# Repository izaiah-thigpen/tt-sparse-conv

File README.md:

# Sparsity-Aware Convolution Core

An 8-bit 3×3 convolution multiply-accumulate core for Tiny Tapeout (SkyWater 130 nm),
controlled over SPI. It skips the switching work of any tap whose pixel or weight is
zero, and counts how many it skipped. It is the silicon half of a wafer-map defect
classifier: on the trained network, 77% of taps have a zero operand.

- [Datasheet: how it works and how to test](docs/info.md)
- [From a wafer to a defect class](docs/wafer_to_class.md): the dataset, how a wafer becomes the network's input, and what each layer does, with pictures

## Layout

| Path | Contents |
| --- | --- |
| `src/project.v` | Tiny Tapeout top level (`tt_um_izaiah_thigpen_sparse_conv`) |
| `src/conv_chip.sv` | SPI interface, command decoder, weight registers |
| `src/mac_core.sv` | Multiply-accumulate core, zero-skip gating, skip counter, output stage |
| `test/test.py` | cocotb tests through the pins only, checked against `test/refmodel.py` |
| `test/refmodel.py` | Bit-exact integer model of the design |
| `test/test_host.py` | Runs the demo-board test program against the design |
| `host/` | Test kit for the fabricated chip: data-to-SPI converter, demo-board test program, test vectors ([guide](host/README.md)) |

## Testing the fabricated chip

See [host/README.md](host/README.md): copy four files and a folder to the Tiny Tapeout demo board and run
one command. It reports PASS or FAIL for every check.

## Run the tests locally

```
cd test
make
```

Needs Icarus Verilog and `pip install -r test/requirements.txt`.

## GitHub Actions

Every push runs the RTL tests, builds the layout with LibreLane, runs Tiny Tapeout's
precheck, reruns the tests on the gate-level netlist, and publishes a layout viewer.
The viewer needs GitHub Pages enabled: Settings → Pages → Source: GitHub Actions.

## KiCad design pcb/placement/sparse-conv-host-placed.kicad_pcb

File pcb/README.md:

# Host board for the sparsity-aware convolution chip

A replacement for the Tiny Tapeout demo board, built to measure the chip's power. It keeps the demo
board v3's RP2350B pin map, so Tiny Tapeout's MicroPython firmware and the `host/` test kit run on it
unchanged, and adds a TI INA228 power monitor on the chip's 1.8 V core supply.

Status: **schematic rev A done; KiCad 9 ERC has 0 errors; starting placement done (`placement/`); routing not started.**

## What is here

| Path | Contents |
| --- | --- |
| `sparse-conv-host/` | The KiCad project: open `sparse-conv-host.kicad_pro` in KiCad 9 (it upgrades the KiCad 7 files) |
| `sparse-conv-host/libs/` | Tiny Tapeout symbols (RP2350B, breakout socket, PMOD host) and footprints (Apache 2.0); `SparseConvHost.pretty` holds the two footprints KiCad 9's libraries lack (RP2350 inductor, INA228 VSSOP-10) |
| `sparse-conv-host-schematic.pdf` | The schematic, 5 pages |
| `gen/design.py` | The design as data: every part, value, footprint, part number and pin-to-net assignment |
| `gen/schgen.py`, `gen/symlib.py`, `gen/sexpr.py` | Writes the KiCad schematic from `design.py` |
| `gen/check_netlist.py`, `gen/check_footprints.py` | Checks KiCad's own exported netlist against the design |
| `placement/` | Starting placement: `sparse-conv-host-placed.kicad_pcb` (all 110 parts placed, 4 layers, design rules set), `placement.csv` (every part's X, Y and rotation) and `placement-preview.png` |
| `gen/placement/` | The script that makes them, from the demo board's arrangement (see its README) |

The schematic is generated, so change `design.py` and rerun `python gen/design.py` rather than editing
connections by hand. Moving symbols around in KiCad for readability is fine; it does not change the nets.
The sheets are drawn net-label style: each pin has a short wire and a label, so the connections are
exactly the ones in `design.py`.

## Sheets

1. **Power:** USB-C, polyfuse, ESD, TLV1117LV33 3.3 V LDO, power LEDs (as on the demo board).
2. **MCU:** RP2350B, W25Q32 flash, 12 MHz crystal, internal core regulator, BOOT and RESET buttons, SWD
   header (copied from the demo board's RP2350B sheet).
3. **Breakout:** the Hirose DF12 60+50-pin socket for the chip's breakout (`TT_HRS_CARRIER_REVC`), MUX
   pull-ups, project reset and clock, three PMOD sockets, a 2×8 logic-analyzer header, 10 MΩ pull-downs
   on the analog pins, mounting holes.
4. **Power monitor:** INA228 across a 0.499 Ω + 4.99 Ω shunt in the core supply, I2C on GPIO12/13,
   ALERT on GPIO15.

## Measuring the chip's core power

The breakout regulates the chip's 1.8 V core itself: AP2112K-1.8 → `VCC_REG` → R14 (0 Ω, 0805) →
`VCCD`. To route the core supply through this board's shunt:

1. On the breakout, remove R14 and solder a 1×12 header into J2.
2. Wire J2 pin 5 (`VCC_REG`) to CORE pin 1, J2 pin 6 (`VCCD`) to CORE pin 2, and ground to CORE pin 3.
3. Normal range: 5.49 Ω, 7.5 mA full scale, 14 nA per step. For more current, fit a jumper on RANGE
   (0.499 Ω, 82 mA full scale).

Without the wires and with R14 in place, the board works exactly like a demo board.

## Checks

- KiCad 7's netlist export reads all sheets; every one of the 99 design nets is one KiCad net with
  exactly the intended pins, every no-connect pin is alone, and no net has a single pin.
- ERC-style rules: every power-input pin has a driver or power flag; no two outputs share a net.
- All 63 used pins of the breakout socket match the Tiny Tapeout demo board, and the socket's power,
  ground, I/O and MUX pins were cross-checked against the SkyWater breakout rev 3.1 schematic.
- Every symbol pin has a pad of the same number in its footprint.

- KiCad 9 ERC: 0 errors. Remaining warnings are harmless: library-copy mismatches (the schematic embeds
  KiCad 7 copies of standard symbols), QSPI_IOVDD typed bidirectional in the Tiny Tapeout RP2350 symbol,
  and the breakout socket's hidden `3v3` pins merging into `+3V3`.

Run `kicad-cli sch export netlist -o board.net sparse-conv-host/sparse-conv-host.kicad_sch`, then
`python gen/check_netlist.py board.net` and `python gen/check_footprints.py`. Run KiCad 9's ERC as well
after opening the project.

## Open items

- Confirm this shuttle's chips ship on SkyWater breakout rev 3.1.
- JLCPCB sourcing for the Hirose DF12NB(5.0)-60DP and -50DP connectors, the RP2350B, the shunts and
  the 10 MΩ resistors (LCSC numbers are filled in only where verified).
- Board outline 100 × 85 mm, corner at (100, 100). The RP2350B sits under the breakout board, as on the demo board.
- Layout: 4 layers; Kelvin traces from the shunt pads to the INA228; follow Raspberry Pi's RP2350
  layout guidance for the crystal, flash and core regulator.

## KiCad 10 note

KiCad 10's `USB_C_Receptacle_HRO_TYPE-C-31-M-12` footprint names the shell pads `SH`; KiCad 7's
symbol calls the shield pin `S1`. In the project, J1's shield pin number was changed to `SH` in the
Symbol Editor so the shell connects to `USB_SHIELD`. If the schematic is ever regenerated from
`design.py`, make the same change again before updating the PCB.

Derived from the [Tiny Tapeout demo board](https://github.com/TinyTapeout/tt-demo-pcb) and
[breakout](https://github.com/TinyTapeout/breakout-pcb) designs, © 2024–2025 Pat Deegan / Psychogenic
Technologies, Apache 2.0.

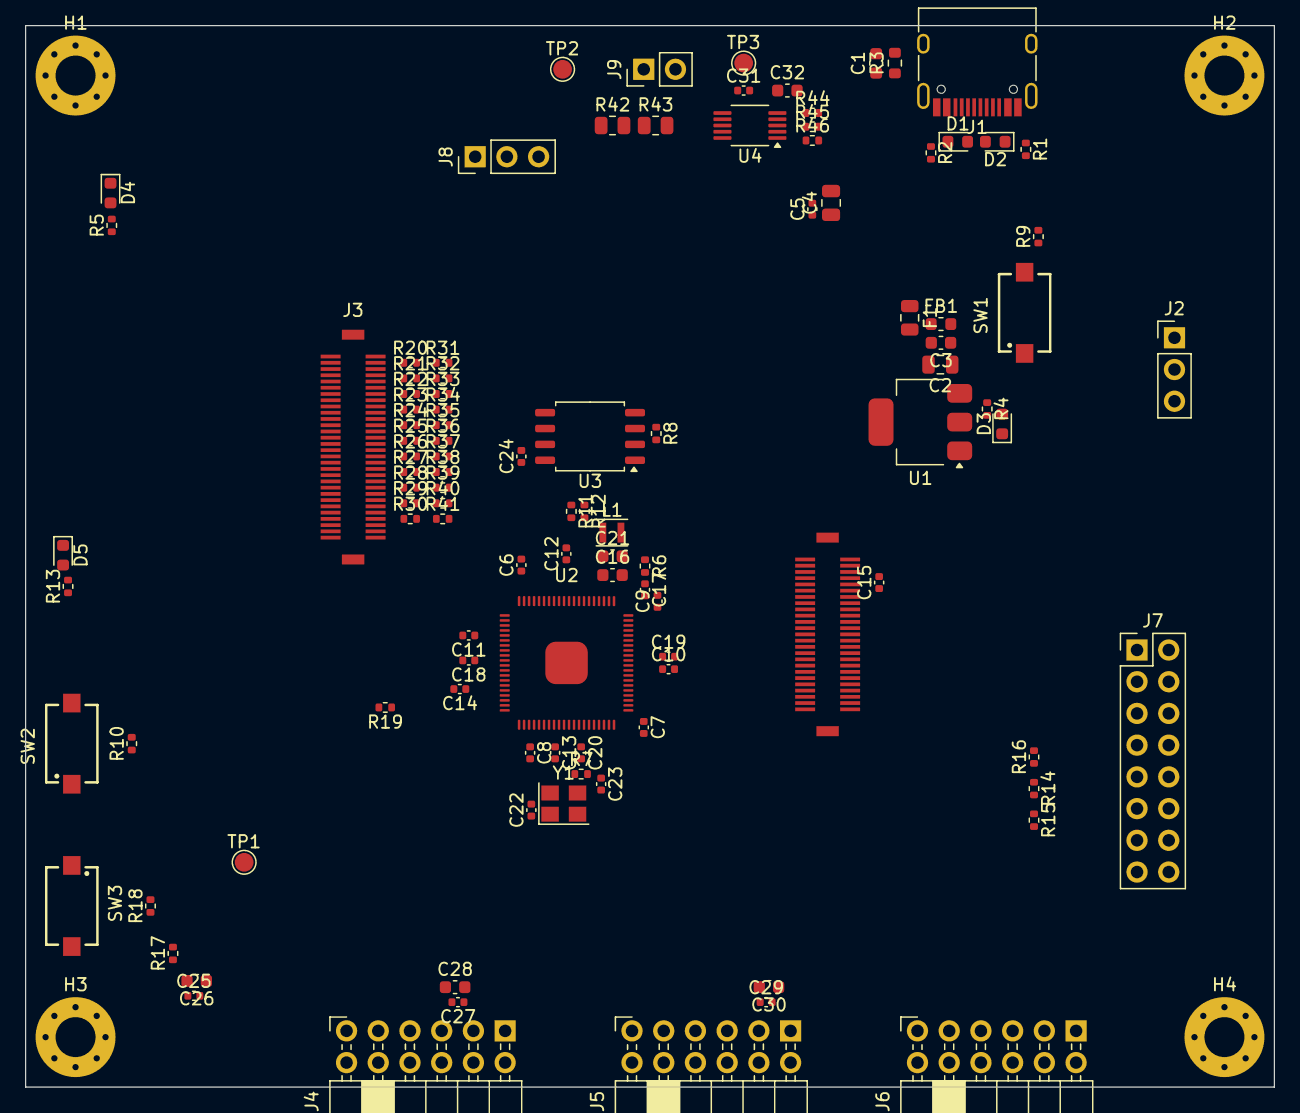
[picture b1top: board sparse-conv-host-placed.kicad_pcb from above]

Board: 4 copper layers, 100.0 x 85.0 mm, 110 parts (0 on the bottom side), 99 nets, no tracks yet.

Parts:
C1, C3, C16, C21, C26, C28, C30, C32: C_0603_1608Metric
C2, C4: C_0805_2012Metric
C5, C6, C7, C8, C9, C10, C11, C12, C13, C14, C15, C17, C18, C19, C20, C22, C23, C24, C25, C27, C29, C31: C_0402_1005Metric
D1, D2: D_0603_1608Metric
D3, D4, D5: LED_0603_1608Metric
F1: Fuse_0805_2012Metric
FB1: L_0603_1608Metric
H1, H2, H3, H4: MountingHole_3.2mm_M3_Pad_Via
J1: USB_C_Receptacle_HRO_TYPE-C-31-M-12
J2, J8: PinHeader_1x03_P2.54mm_Vertical
J3: TT; TT_HRS_CARRIER_REVC
J4, J5, J6: PinSocket_2x06_P2.54mm_PMODHost1A
J7: PinHeader_2x08_P2.54mm_Vertical
J9: PinHeader_1x02_P2.54mm_Vertical
L1: L_Murata_DFE201610P
R1, R2, R4, R5, R6, R7, R8, R9, R10, R11, R12, R13, R14, R15, R16, R17, R18, R19, R20, R21, R22, R23, R24, R25, R26, R27, R28, R29, R30, R31, R32, R33, R34, R35, R36, R37, R38, R39, R40, R41, R44, R45, R46: R_0402_1005Metric
R3: R_0603_1608Metric
R42, R43: R_0805_2012Metric
SW1, SW2, SW3: 434121025816
TP1, TP2, TP3: TestPoint_Pad_D1.5mm
U1: SOT-223-3_TabPin2
U2: QFN; QFN-80-1EP_10x10mm_P0.4mm_EP3.4x3.4mm
U3: SOIC-8_5.275x5.275mm_P1.27mm
U4: VSSOP-10_3x3mm_P0.5mm
Y1: Crystal_SMD_3225-4Pin_3.2x2.5mm

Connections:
+1V1: C18.1, C19.1, C20.1, C21.1, L1.1, U2.10, U2.32, U2.51, U2.65
+3V3: C4.1, C5.1, C6.1, C7.1, C8.1, C9.1, C10.1, C11.1, C12.1, C13.1, C14.1, C15.1, C16.1, C24.1, C25.1, C26.1, C27.1, C28.1, C29.1, C30.1, C31.1, C32.1, J3.L1, J3.R8, J3.R10, J4.6, J4.12, J5.6, J5.12, J6.6, J6.12, R5.1, R6.1, R8.1, R10.1, R14.1, R15.1, R16.1, R18.1, R44.1, R45.1, R46.1, U1.2, U2.5, U2.15, U2.24, U2.29, U2.41, U2.50, U2.59, U2.60, U2.64, U2.68, U2.69, U2.76, U3.8, U4.6
+5V: C2.1, C3.1, FB1.2, J3.R2, J3.R4, R4.1, U1.3
/Chip breakout sockets and I/O/AN0: J3.L2, R20.1
/Chip breakout sockets and I/O/AN1: J3.L4, R21.1
/Chip breakout sockets and I/O/AN2: J3.L6, R22.1
/Chip breakout sockets and I/O/AN3: J3.L10, R23.1
/Chip breakout sockets and I/O/AN4: J3.L12, R24.1
/Chip breakout sockets and I/O/AN5: J3.L14, R25.1
/Chip breakout sockets and I/O/AN6: J3.L18, R26.1
/Chip breakout sockets and I/O/AN7: J3.L20, R27.1
/Chip breakout sockets and I/O/AN8: J3.L22, R28.1
/Chip breakout sockets and I/O/AN9: J3.L26, R29.1
/Chip breakout sockets and I/O/AN10: J3.L28, R30.1
/Chip breakout sockets and I/O/AN11: J3.L30, R31.1
/Chip breakout sockets and I/O/AN12: J3.L34, R32.1
/Chip breakout sockets and I/O/AN13: J3.L36, R33.1
/Chip breakout sockets and I/O/AN14: J3.L38, R34.1
/Chip breakout sockets and I/O/AN15: J3.L42, R35.1
/Chip breakout sockets and I/O/AN16: J3.L44, R36.1
/Chip breakout sockets and I/O/AN17: J3.L46, R37.1
/Chip breakout sockets and I/O/AN18: J3.L50, R38.1
/Chip breakout sockets and I/O/AN19: J3.L52, R39.1
/Chip breakout sockets and I/O/AN20: J3.L54, R40.1
/Chip breakout sockets and I/O/AN21: J3.L58, R41.1
/Chip breakout sockets and I/O/PROJ_CLK: J3.L57, J7.9, R19.2, TP1.1
/Chip breakout sockets and I/O/PROJ_RST_N: J3.L53, J7.11, R17.2, R18.2, SW3.1
/Chip core power monitor/SHUNT_MID: J9.1, R42.2, R43.1
/Chip core power monitor/VCORE_IN: J8.1, R42.1, TP2.1, U4.10
/Chip core power monitor/VCORE_OUT: J8.2, J9.2, R43.2, TP3.1, U4.8, U4.9
/RP2350B microcontroller/BOOT_SW: R9.2, SW1.1
/RP2350B microcontroller/QSPI_SCLK: U2.71, U3.6
/RP2350B microcontroller/QSPI_SD0: U2.72, U3.5
/RP2350B microcontroller/QSPI_SD1: U2.74, U3.2
/RP2350B microcontroller/QSPI_SD2: U2.73, U3.3
/RP2350B microcontroller/QSPI_SD3: U2.70, U3.7
/RP2350B microcontroller/QSPI_SS: R8.2, R9.1, U2.75, U3.1
/RP2350B microcontroller/RP_LED: R13.1, U2.9
/RP2350B microcontroller/RP_LED_A: D5.2, R13.2
/RP2350B microcontroller/RUN: R10.2, SW2.1, U2.35
/RP2350B microcontroller/SWCLK: J2.1, U2.33
/RP2350B microcontroller/SWDIO: J2.3, U2.34
/RP2350B microcontroller/USB_DM_MCU: R12.2, U2.66
/RP2350B microcontroller/USB_DP_MCU: R11.2, U2.67
/RP2350B microcontroller/VREG_AVDD: C17.1, R6.2, U2.61
/RP2350B microcontroller/VREG_LX: L1.2, U2.63
/RP2350B microcontroller/XIN: C22.1, U2.30, Y1.1
/RP2350B microcontroller/XOUT: R7.1, U2.31
/RP2350B microcontroller/XOUT_R: C23.1, R7.2, Y1.3
/USB-C input and 3.3 V supply/CC1: J1.A5, R1.1
/USB-C input and 3.3 V supply/CC2: J1.B5, R2.1
/USB-C input and 3.3 V supply/LED_3V3: D4.2, R5.2
/USB-C input and 3.3 V supply/LED_USB: D3.2, R4.2
/USB-C input and 3.3 V supply/USB_SHIELD: C1.1, J1.S1, R3.1
/USB-C input and 3.3 V supply/VBUS_F: F1.2, FB1.1
/USB-C input and 3.3 V supply/VBUS_RAW: F1.1, J1.A4, J1.A9, J1.B4, J1.B9
CTRL_ENA: J3.R46, R14.2, U2.77
CTRL_SEL_INC: J3.R47, R15.2, U2.79
CTRL_SEL_RST_N: J3.R43, R16.2, U2.78
GND: C1.2, C2.2, C3.2, C4.2, C5.2, C6.2, C7.2, C8.2, C9.2, C10.2, C11.2, C12.2, C13.2, C14.2, C15.2, C16.2, C17.2, C18.2, C19.2, C20.2, C21.2, C22.2, C23.2, C24.2, C25.2, C26.2, C27.2, C28.2, C29.2, C30.2, C31.2, C32.2, D1.2, D2.2, D3.1, D4.1, D5.1, H1.1, H2.1, H3.1, H4.1, J1.A1, J1.A12, J1.B1, J1.B12, J2.2, J3.L3, J3.L8, J3.L11, J3.L16, J3.L19, J3.L24, J3.L27, J3.L32, J3.L35, J3.L40, J3.L43, J3.L48, J3.L51, J3.L55, J3.L56, J3.L59, J3.R1, J3.R6, J3.R11, J3.R12, J3.R20, J3.R21, J3.R28, J3.R33, J3.R38, J3.R41, J3.R44, J3.R45, J3.R48, J4.5, J4.11, J5.5, J5.11, J6.5, J6.11, J7.13, J7.15, J8.3, R1.2, R2.2, R3.2, R20.2, R21.2, R22.2, R23.2, R24.2, R25.2, R26.2, R27.2, R28.2, R29.2, R30.2, R31.2, R32.2, R33.2, R34.2, R35.2, R36.2, R37.2, R38.2, R39.2, R40.2, R41.2, SW1.2, SW2.2, SW3.2, U1.1, U2.62, U2.81, U3.4, U4.1, U4.2, U4.7, Y1.2, Y1.4
I2C_SCL: R45.2, U2.12, U4.5
I2C_SDA: R44.2, U2.11, U4.4
MNG0: J3.R42, U2.80
MNG1: J3.R40, U2.1
MNG2: J3.R36, U2.2
MNG3: J3.R30, U2.3
MNG4: J3.R26, U2.4
MNG5: J3.R22, U2.6
MNG6: J3.R18, U2.7
MNG7: J3.R16, U2.8
PM_ALERT: R46.2, U2.14, U4.3
PROJ_CLK_RP: R19.1, U2.16
PROJ_RST_RP: R17.1, U2.13
UIO0: J3.L5, J5.1, U2.26
UIO1: J3.L7, J5.2, U2.27
UIO2: J3.L9, J5.3, U2.28
UIO3: J3.L13, J5.4, U2.36
UIO4: J3.L15, J5.7, U2.37
UIO5: J3.L17, J5.8, U2.38
UIO6: J3.L21, J5.9, U2.39
UIO7: J3.L23, J5.10, U2.40
UI_IN0: J3.L31, J4.1, J7.1, U2.17
UI_IN1: J3.L33, J4.2, J7.3, U2.18
UI_IN2: J3.L37, J4.3, J7.5, U2.19
UI_IN3: J3.L39, J4.4, J7.7, U2.20
UI_IN4: J3.L41, J4.7, U2.21
UI_IN5: J3.L45, J4.8, U2.22
UI_IN6: J3.L47, J4.9, U2.23
UI_IN7: J3.L49, J4.10, U2.25
UO_OUT0: J3.R19, J6.1, J7.2, U2.42
UO_OUT1: J3.R17, J6.2, J7.4, U2.43
UO_OUT2: J3.R15, J6.3, J7.6, U2.44
UO_OUT3: J3.R13, J6.4, J7.8, U2.45
UO_OUT4: J3.R9, J6.7, J7.10, U2.46
UO_OUT5: J3.R7, J6.8, J7.12, U2.47
UO_OUT6: J3.R5, J6.9, J7.14, U2.48
UO_OUT7: J3.R3, J6.10, J7.16, U2.49
USB_DM: D2.1, J1.A7, J1.B7, R12.1
USB_DP: D1.1, J1.A6, J1.B6, R11.1

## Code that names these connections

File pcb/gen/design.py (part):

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
prj = Project('sparse-conv-host', 'Sparse Convolution Chip Host Board', 'A', 'Izaiah Thigpen', '2026-10-22')
prj.root_note = ('Host board for the sparsity-aware convolution chip (Tiny Tapeout, SkyWater 130 nm).\n'
                 'Keeps the Tiny Tapeout demo board v3 RP2350B pin map, so its firmware and the host/ test kit run unchanged,\n'
                 'and adds an INA228 power monitor on the chip core supply. Demo board design (c) 2025 Pat Deegan, Apache 2.0.')

# ================================================================== sheet 1: USB and power
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# ================================================================== sheet 2: RP2350B
mcu = prj.sheet('MCU', 'mcu.kicad_sch', 'RP2350B microcontroller', paper='A2')
gpio = {i: None for i in range(48)}
gpio.update({0: 'CTRL_ENA', 1: 'CTRL_SEL_RST_N', 2: 'CTRL_SEL_INC', 11: 'RP_LED',
             12: 'I2C_SDA', 13: 'I2C_SCL', 14: 'PROJ_RST_RP', 15: 'PM_ALERT', 16: 'PROJ_CLK_RP'})
gpio.update({3 + k: f'MNG{k}' for k in range(8)})
gpio.update({17 + k: f'UI_IN{k}' for k in range(8)})
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        R('510', 'RP_LED', 'RP_LED_A', MPN='RC0402FR-07510RL', LCSC='C276273'),
        led('RP_LED_A', 'GND'))
mcu.note('Copied from the Tiny Tapeout demo board v3 RP2350B sheet. GPIO map (unchanged, so the TT firmware runs as is):\n'
         'GPIO0 ctrl_ena, GPIO1 ctrl_sel_rst_n, GPIO2 ctrl_sel_inc, GPIO3-10 management (breakout ID EEPROM on GPIO4/5),\n'
         'GPIO11 LED, GPIO14 project reset, GPIO16 project clock, GPIO17-24 ui_in, GPIO25-32 uio, GPIO33-40 uo_out.\n'
         'New: GPIO12/13 I2C to the INA228 power monitor, GPIO15 its ALERT.')

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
